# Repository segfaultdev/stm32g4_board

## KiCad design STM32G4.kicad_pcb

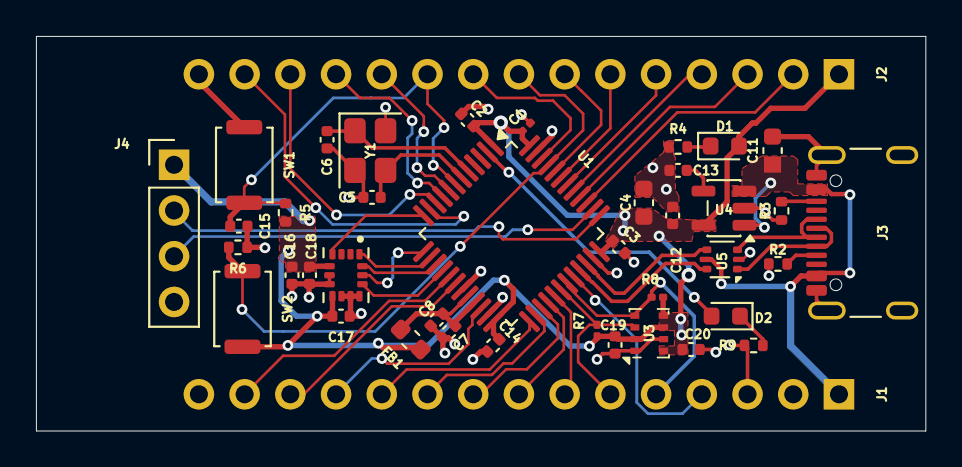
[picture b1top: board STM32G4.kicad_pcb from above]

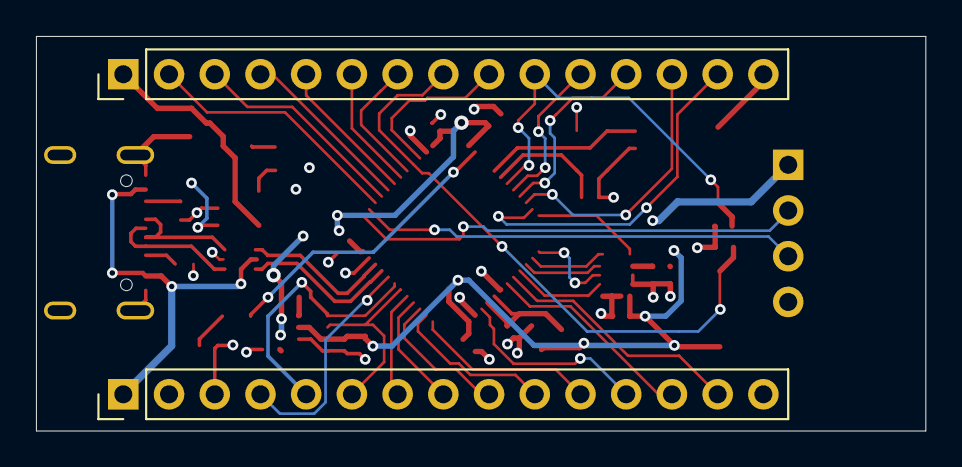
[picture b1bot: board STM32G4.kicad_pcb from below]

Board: 4 copper layers, 49.4 x 21.9 mm, 41 parts (2 on the bottom side), 47 nets.

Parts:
C1: .1uF; C_0201_0603Metric
C2, C3, C7, C14, C17, C18, C19, C20: .1uF; C_0402_1005Metric
C4: 4.7uF; C_0603_1608Metric
C5, C6, C15: C; C_0402_1005Metric
C8: 1uF; C_0402_1005Metric
C11: 10uF; C_0603_1608Metric
C12: 10uF; C_0402_1005Metric
C13: 10nF; C_0402_1005Metric
C16: 2.2uF; C_0402_1005Metric
D1: PWR_LED; LED_0603_1608Metric
D2: USR_LED; LED_0603_1608Metric
FB1: FCM1608KF-601T03; L_0603_1608Metric
J1, J2: Conn_01x15; PinHeader_1x15_P2.54mm_Vertical
J3: USB_C_Receptacle_USB2.0_16P; USB_C_Receptacle_GCT_USB4105-xx-A_16P_TopMnt_Horizontal
J4: Conn_01x04_Pin; PinHeader_1x04_P2.54mm_Vertical
R2, R3: 5k1; R_0402_1005Metric
R4, R9: 330R; R_0402_1005Metric
R5, R6: 10k; R_0402_1005Metric
R7, R8: 4k7; R_0201_0603Metric
SW1, SW2: RST_SW; SW_Push_SPST_NO_Alps_SKRK
U1: STM32G491CETx; LQFP-48_7x7mm_P0.5mm
U2: ICM-42688-P; PQFN50P300X250X97-14N
U3: BMP280; Bosch_LGA-8_2x2.5mm_P0.65mm_ClockwisePinNumbering
U4: SPX3819M5-L-3-3; SOT-23-5
U5: USBLC6-2P6; SOT-666
Y1: 25MHz; Crystal_SMD_3225-4Pin_3.2x2.5mm

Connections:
+3.3V: C1.2, C2.2, C3.2, C4.2, C12.2, C14.2, C16.2, C17.2, C18.2, C19.1, C20.2, D1.2 (A), FB1.1, J2.1, J4.1, R5.1, R7.2, R8.1, SW2.1, U1.1 (VBAT), U1.24 (VDD), U1.36 (VDD), U1.48 (VDD), U2.5 (VDDIO), U2.8 (VDD), U3.2 (CSB), U3.5 (SDO), U3.6 (VDDIO), U3.8 (VDD), U4.5 (OUT)
/HSE_IN: C6.2, U1.5 (PF0), Y1.1
/HSE_OUT: C5.1, U1.6 (PF1), Y1.3
/I2C1_SCL: J1.5, R8.2, U1.31 (PA9), U3.4 (SCK)
/I2C1_SDA: J1.6, R7.1, U1.30 (PA8), U3.3 (SDI)
/MISO: U1.14 (PA6), U2.1 (AP_SDO/AP_AD0)
/MOSI: U1.15 (PA7), U2.14 (AP_SDA/AP_SDIO/AP_SDI)
/NSS: U1.16 (PB0), U2.12 (AP_CS)
/PA0: J2.11, U1.8 (PA0)
/PA1: J2.12, U1.9 (PA1)
/PA2: J2.13, U1.10 (PA2)
/PA3: J2.14, U1.11 (PA3)
/PA4: U1.12 (PA4), U2.4 (INT1/INT)
/PA10: J1.4, U1.32 (PA10)
/PA15: J2.2, U1.39 (PA15)
/PB1: J1.14, U1.17 (PB1)
/PB2: J1.13, U1.18 (PB2)
/PB3: J2.3, U1.40 (PB3)
/PB4: J2.4, U1.41 (PB4)
/PB5: J2.5, U1.42 (PB5)
/PB6: J2.6, U1.43 (PB6)
/PB7: J2.7, U1.44 (PB7)
/PB9: J2.9, U1.46 (PB9)
/PB10: J1.12, U1.22 (PB10)
/PB11: J1.11, U1.25 (PB11)
/PB12: J1.10, U1.26 (PB12)
/PB13: J1.9, U1.27 (PB13)
/PB14: J1.8, U1.28 (PB14)
/PB15: J1.7, U1.29 (PB15)
/PC13: D2.2 (A), U1.2 (PC13)
/SSCLK: U1.13 (PA5), U2.13 (AP_SCL/AP_SCLK)
/SWCLK: J4.3, U1.38 (PA14)
/SWDIO: J4.2, U1.37 (PA13)
/USBD+: U1.34 (PA12), U5.4 (I/O2)
/USBD-: U1.33 (PA11), U5.6 (I/O1)
BOOT0: J2.8, R6.2, SW2.2, U1.45 (PB8)
GND: C1.1, C2.1, C3.1, C4.1, C5.2, C6.1, C7.1, C8.1, C11.1, C12.1, C13.1, C14.1, C15.1, C16.1, C17.1, C18.1, C19.2, C20.1, J1.2, J1.3, J1.15, J2.15, J3.A1 (GND), J3.A12 (GND), J3.B1 (GND), J3.B12 (GND), J3.S1 (SHIELD), J4.4, R2.1, R3.2, R4.2, R6.1, R9.2, SW1.1, U1.19 (VSSA), U1.23 (VSS), U1.35 (VSS), U1.47 (VSS), U2.6 (GND), U2.7 (RESV_7), U2.9 (INT2/FSYNC/CLKIN), U2.10 (RESV_10), U2.11 (RESV_11), U3.1 (GND), U3.7 (GND), U4.2 (GND), U5.2 (GND), Y1.2, Y1.4
NRST: C15.2, J2.10, R5.2, SW1.2, U1.7 (PG10)
unnamed: D1.1 (K), R4.1
unnamed: D2.1 (K), R9.1
unnamed: J3.A5 (CC1), R2.2
unnamed: J3.B5 (CC2), R3.1
unnamed: J3.A6 (D+), J3.B6 (D+), U5.3 (I/O2)
unnamed: J3.A7 (D-), J3.B7 (D-), U5.1 (I/O1)
unnamed: C13.2, U4.4 (BP)
VBUS: C11.2, J1.1, J3.A4 (VBUS), J3.A9 (VBUS), J3.B4 (VBUS), J3.B9 (VBUS), U4.1 (IN), U4.3 (EN), U5.5 (VBUS)
VREF: C7.2, C8.2, FB1.2, U1.20 (VREF+), U1.21 (VDDA)

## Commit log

2025-11-25 Second Commit
